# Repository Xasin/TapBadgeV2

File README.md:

# TapBadgeV2
The second, far more ambitious version of the TapBadge wearable

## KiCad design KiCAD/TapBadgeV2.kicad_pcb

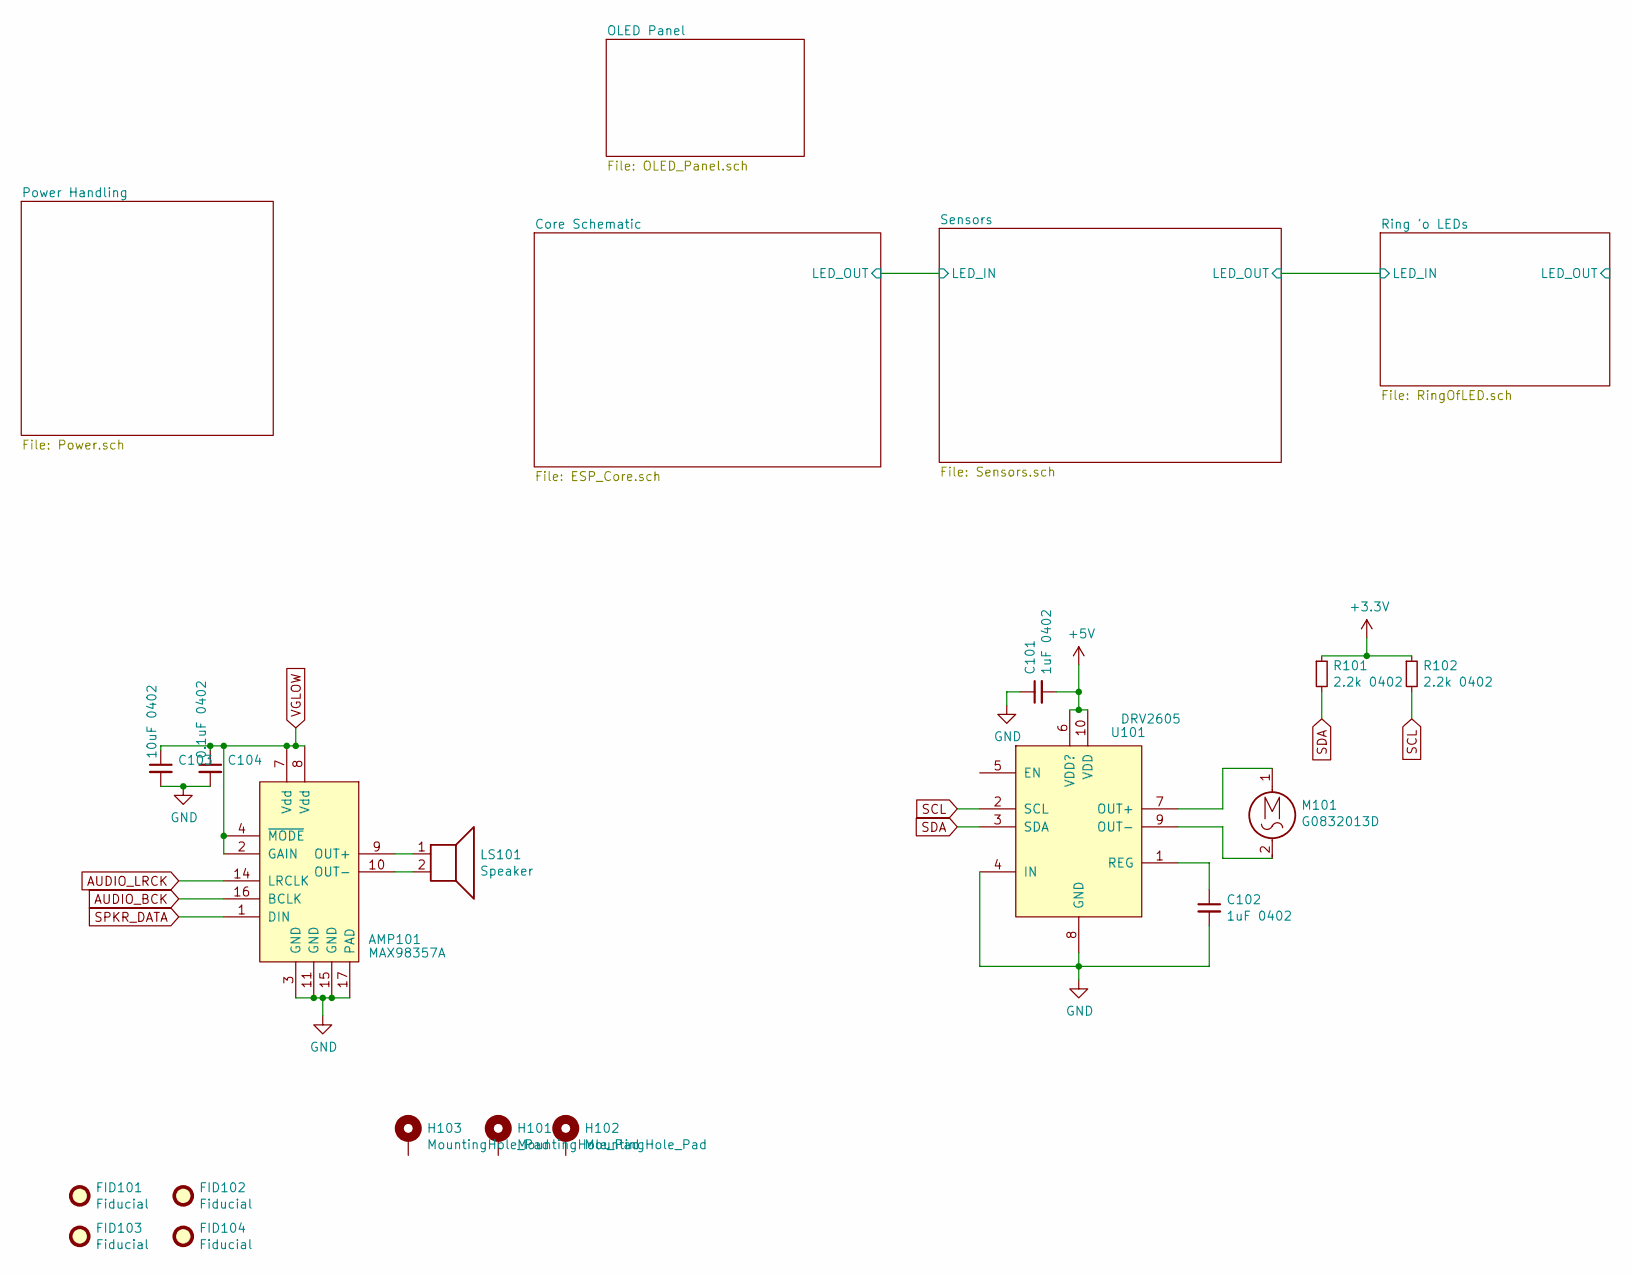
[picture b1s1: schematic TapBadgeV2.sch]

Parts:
AMP101: MAX98357A; QFN-16-1EP_3x3mm_P0.5mm_EP1.9x1.9mm_ThermalVias
C101, C102: 1uF 0402; C_0402_1005Metric
C103: 10uF 0402; C_0402_1005Metric
C104: 0.1uF 0402; C_0402_1005Metric
FID101, FID102, FID103, FID104: Fiducial; Fiducial_1mm_Mask2mm
H101, H102, H103: MountingHole_Pad; MountingHole_1.5mm_M1_Pad_Via
LS101: Speaker; SP-1609S-1
M101: G0832013D; PinHeader_1x02_P2.00mm_Vertical
R101, R102: 2.2k 0402; R_0402_1005Metric
U101: DRV2605; VSSOP-10_3x3mm_P0.5mm

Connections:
+3V3: R101.1, R102.1; also elsewhere on the board
AUDIO_BCK: AMP101.16 (BCLK); also elsewhere on the board
AUDIO_LRCK: AMP101.14 (LRCLK); also elsewhere on the board
GND: AMP101.3 (GND), AMP101.11 (GND), AMP101.15 (GND), AMP101.17 (PAD), C101.1, C102.2, C103.2, C104.2, H101.1, H102.1, H103.1, U101.4 (IN), U101.8 (GND); also elsewhere on the board
unnamed: AMP101.9 (OUT+), LS101.1
unnamed: AMP101.10 (OUT-), LS101.2
unnamed: C102.1, U101.1 (REG)
unnamed: M101.1, U101.7 (OUT+)
unnamed: M101.2, U101.9 (OUT-)
SCL: R102.2, U101.2 (SCL); also elsewhere on the board
SPKR_DATA: AMP101.1 (DIN); also elsewhere on the board

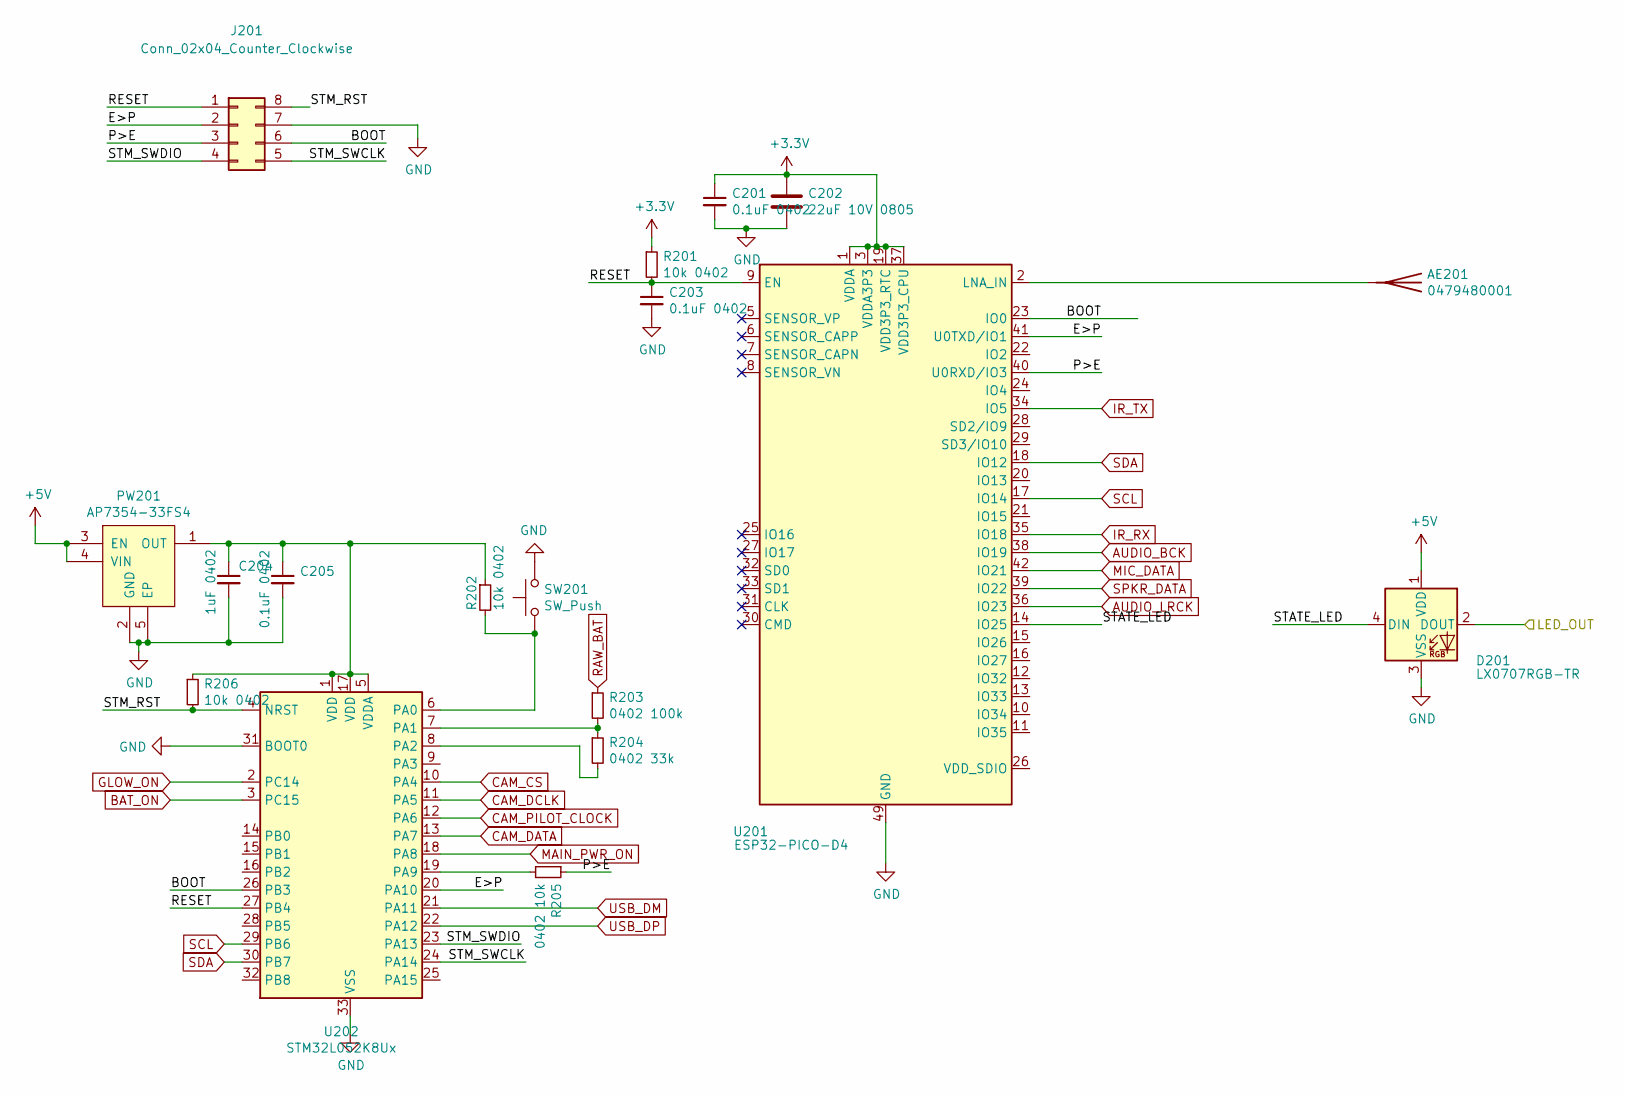
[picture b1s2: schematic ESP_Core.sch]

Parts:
AE201: 0479480001
C201, C203, C205: 0.1uF 0402; C_0402_1005Metric
C202: 22uF 10V 0805; C_0805_2012Metric
C204: 1uF 0402; C_0402_1005Metric
D201: LX0707RGB-TR; SMD-LX0707RGB-TR
J201: Conn_02x04_Counter_Clockwise; SOIC_clipProgSmall
PW201: AP7354-33FS4; X2-DFN1010-4
R201, R202, R206: 10k 0402; R_0402_1005Metric
R203: 0402 100k; R_0402_1005Metric
R204: 0402 33k; R_0402_1005Metric
R205: 0402 10k; R_0402_1005Metric
SW201: SW_Push; SW_SPST_B3U-1000P
U201: ESP32-PICO-D4; QFN-48-1EP_7x7mm_P0.5mm_EP5.3x5.3mm
U202: STM32L052K8Ux; QFN-32-1EP_5x5mm_P0.5mm_EP3.45x3.45mm

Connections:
+3V3: C201.1, C202.1, R201.1, U201.1 (VDDA), U201.3 (VDDA3P3), U201.4 (VDDA3P3), U201.19 (VDD3P3_RTC), U201.37 (VDD3P3_CPU), U201.43 (VDDA), U201.46 (VDDA); also elsewhere on the board
/Core Schematic/BOOT: J201.6, U201.23 (IO0), U202.26 (PB3)
/Core Schematic/E>P: J201.2, U201.41 (U0TXD/IO1), U202.20 (PA10)
/Core Schematic/ESP_GLOW_ON: U201.24 (IO4); also elsewhere on the board
/Core Schematic/EXT_1: U201.20 (IO13); also elsewhere on the board
/Core Schematic/EXT_2: U201.21 (IO15); also elsewhere on the board
/Core Schematic/P>E: J201.3, R205.1, U201.40 (U0RXD/IO3)
/Core Schematic/RESET: C203.1, J201.1, R201.2, U201.9 (EN), U202.27 (PB4)
/Core Schematic/STM_GLOW: U202.2 (PC14); also elsewhere on the board
/Core Schematic/STM_RST: J201.8, R206.2, U202.4 (NRST)
/Core Schematic/STM_SWCLK: J201.5, U202.24 (PA14)
/Core Schematic/STM_SWDIO: J201.4, U202.23 (PA13)
/Sensors/LED_IN: D201.2 (DOUT); also elsewhere on the board
AUDIO_BCK: U201.38 (IO19); also elsewhere on the board
AUDIO_LRCK: U201.15 (IO26); also elsewhere on the board
BAT_ON: U202.3 (PC15); also elsewhere on the board
CAM_CS: U202.10 (PA4); also elsewhere on the board
CAM_DATA: U202.13 (PA7); also elsewhere on the board
CAM_DCLK: U202.11 (PA5); also elsewhere on the board
CAM_PILOT_CLOCK: U202.12 (PA6); also elsewhere on the board
GND: C201.2, C202.2, C203.2, C204.2, C205.2, D201.3 (VSS), J201.7, PW201.2 (GND), PW201.5 (EP), SW201.2, U201.49 (GND), U202.31 (BOOT0), U202.33 (VSS); also elsewhere on the board
IR_RX: U201.16 (IO27); also elsewhere on the board
IR_TX: U201.34 (IO5); also elsewhere on the board
KNOCK_INT: U201.12 (IO32); also elsewhere on the board
MAIN_PWR_ON: U202.18 (PA8); also elsewhere on the board
unnamed: AE201.1, U201.2 (LNA_IN)
unnamed: C204.1, C205.1, PW201.1 (OUT), R202.1, R206.1, U202.1 (VDD), U202.5 (VDDA), U202.17 (VDD)
unnamed: R202.2, SW201.1, U202.6 (PA0)
unnamed: R203.2, R204.1, U202.7 (PA1)
unnamed: R204.2, U202.8 (PA2)
unnamed: R205.2, U202.19 (PA9)
RAW_BAT: R203.1; also elsewhere on the board
SCL: U201.17 (IO14), U202.29 (PB6); also elsewhere on the board
SPKR_DATA: U201.39 (IO22); also elsewhere on the board
USB_DM: U202.21 (PA11); also elsewhere on the board
USB_DP: U202.22 (PA12); also elsewhere on the board
~CHG: U202.16 (PB2); also elsewhere on the board
~VUSB_PRESENT: U202.14 (PB0); also elsewhere on the board

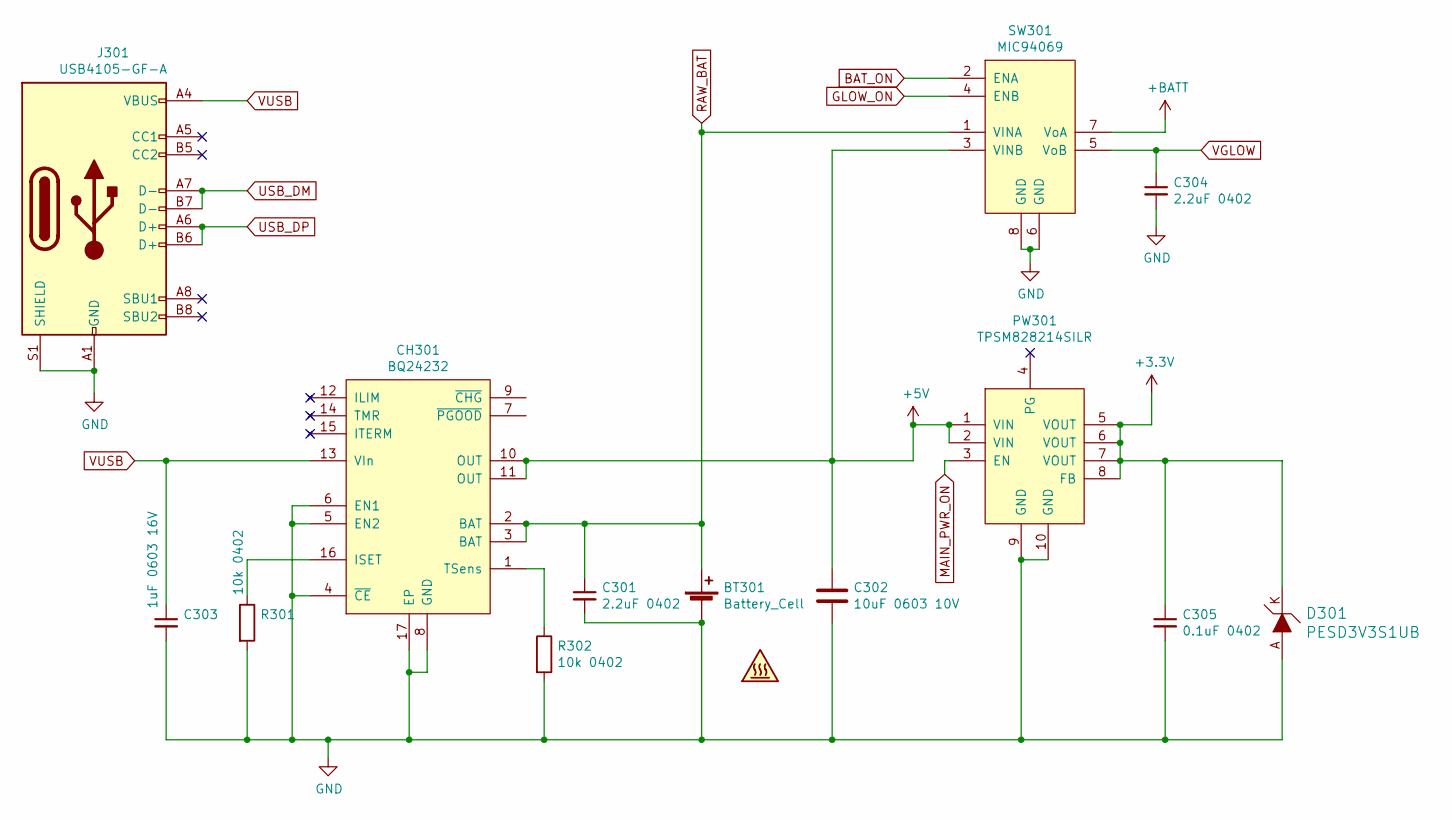
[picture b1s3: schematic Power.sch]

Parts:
BAT301: SYM_Hot_Small; LiPo_150mAh
BT301: Battery_Cell; JST_PH_S2B-PH-SM4-TB_1x02-1MP_P2.00mm_Horizontal
C301, C304: 2.2uF 0402; C_0402_1005Metric
C302: 10uF 0603 10V; C_0603_1608Metric
C303: 1uF 0603 16V; C_0603_1608Metric
C305: 0.1uF 0402; C_0402_1005Metric
CH301: BQ24232; VQFN-16-1EP_3x3mm_P0.5mm_EP1.6x1.6mm_ThermalVias
D301: PESD3V3S1UB; SOD-523; MPN ESD5Z3.3T1G; Digi-Key_PN ESD5Z3.3T1GOSCT-ND
J301: USB4105-GF-A; USB_C_Receptacle_HRO_TYPE-C-31-M-12
PW301: TPSM828214SILR; uSIP-10
R301, R302: 10k 0402; R_0402_1005Metric
SW301: MIC94069; MLF-6-EP-P0.5mm

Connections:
+3V3: C305.1, D301.K, PW301.5 (VOUT), PW301.6 (VOUT), PW301.7 (VOUT), PW301.8 (FB); also elsewhere on the board
+BATT: SW301.7 (VoA); also elsewhere on the board
GLOW_ON: SW301.4 (ENB); also elsewhere on the board
GND: BT301.2 (-), C301.2, C302.2, C303.2, C304.2, C305.2, CH301.4 (~CE), CH301.5 (EN2), CH301.6 (EN1), CH301.8 (GND), CH301.17 (EP), D301.A, J301.A1 (GND), J301.A12 (GND), J301.B1 (GND), J301.B12 (GND), J301.S1 (SHIELD), PW301.9 (GND), PW301.10 (GND), R301.2, R302.2, SW301.6 (GND), SW301.8 (GND); also elsewhere on the board
unnamed: CH301.1 (TSens), R302.1
unnamed: CH301.16 (ISET), R301.1
unnamed 73: PW301.3 (EN); also elsewhere on the board
unnamed 74: SW301.2 (ENA); also elsewhere on the board
RAW_BAT: BT301.1 (+), C301.1, CH301.2 (BAT), CH301.3 (BAT), SW301.1 (VINA); also elsewhere on the board
USB_DM: J301.A7 (D-), J301.B7 (D-); also elsewhere on the board
USB_DP: J301.A6 (D+), J301.B6 (D+); also elsewhere on the board
VUSB: C303.1, CH301.13 (VIn), J301.A4 (VBUS), J301.A9 (VBUS), J301.B4 (VBUS), J301.B9 (VBUS); also elsewhere on the board
~CHG: CH301.9 (~CHG); also elsewhere on the board
~VUSB_PRESENT: CH301.7 (~PGOOD); also elsewhere on the board

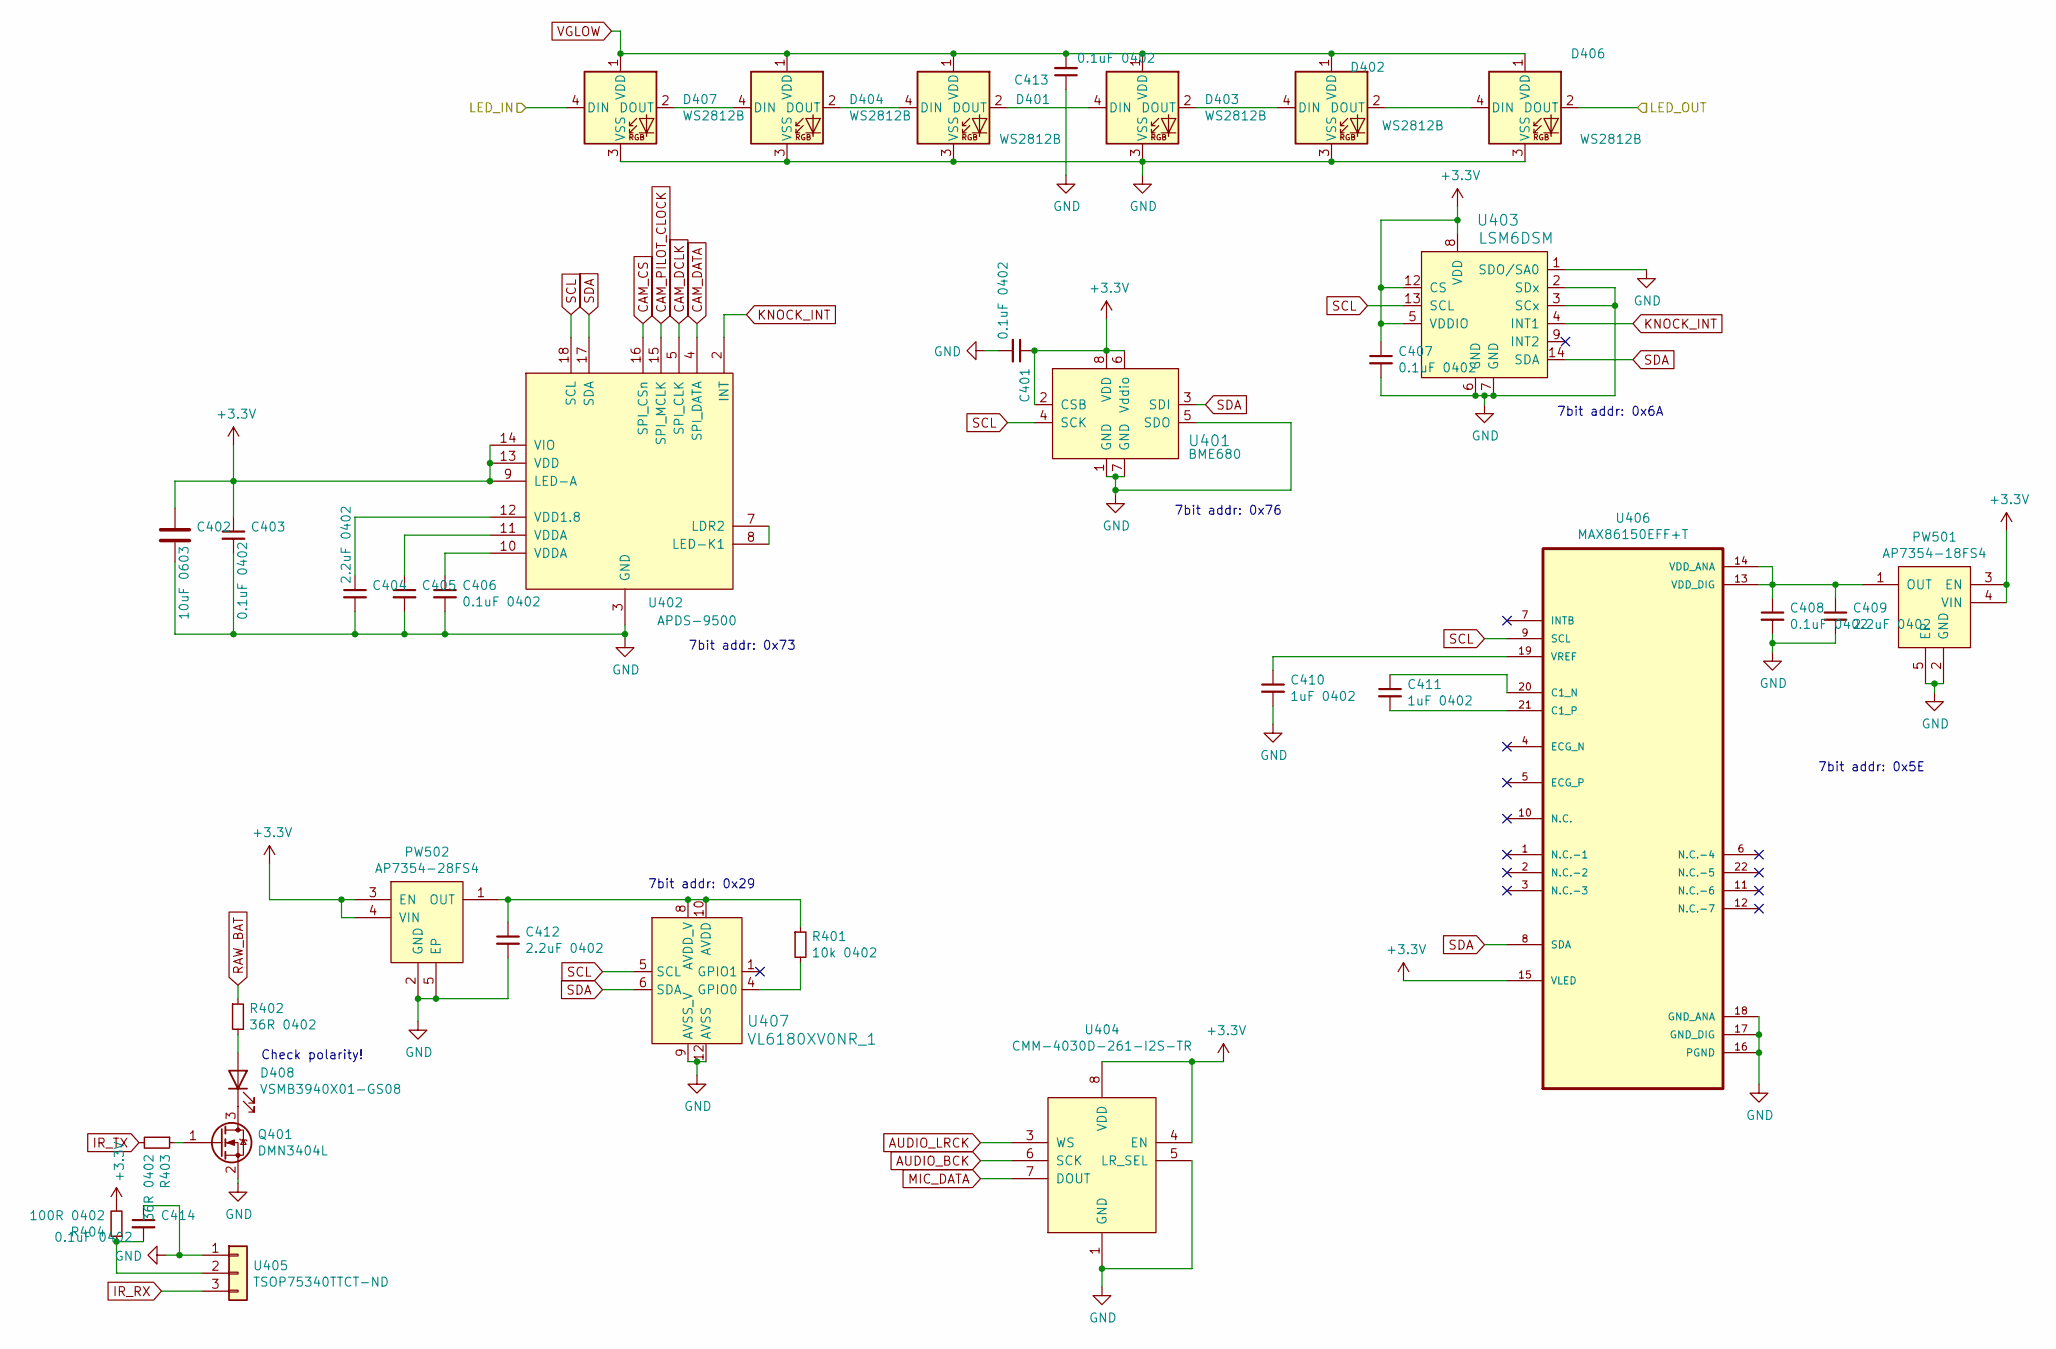
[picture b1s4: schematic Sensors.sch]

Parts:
C401, C403, C405, C406, C407, C408, C413, C414: 0.1uF 0402; C_0402_1005Metric
C402: 10uF 0603; C_0603_1608Metric
C404, C409, C412: 2.2uF 0402; C_0402_1005Metric
C410, C411: 1uF 0402; C_0402_1005Metric
D401, D402, D403, D404, D406, D407: WS2812B; SMD-LX0707RGB-TR
D408: VSMB3940X01-GS08; LED_PLCC-2
PW501: AP7354-18FS4; X2-DFN1010-4
PW502: AP7354-28FS4; X2-DFN1010-4
Q401: DMN3404L; SOT-23
R401: 10k 0402; R_0402_1005Metric
R402, R403: 36R 0402; R_0402_1005Metric
R404: 100R 0402; R_0402_1005Metric
U401: BME680; MPN BME680; Digi-Key_PN 828-1077-1-ND
U402: APDS-9500
U403: LSM6DSM; LGA-14L_2.5x3mm__LSM6DS3; MPN LSM6DS3TR; Digi-Key_PN 497-15383-1-ND
U404: CMM-4030D-261-I2S-TR; CMM-4030
U405: TSOP75340TTCT-ND; TSOP75xxx
U406: MAX86150EFF+T; XDCR_MAX86150EFF+
U407: VL6180XV0NR_1; LGA-12_4.8x2.8_VL6180; MPN VL6180XV0NR/1; Digi-Key_PN 497-14702-1-ND

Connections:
+3V3: C401.1, C402.1, C403.1, C407.1, PW501.3 (EN), PW501.4 (VIN), PW502.3 (EN), PW502.4 (VIN), R404.2, U401.2 (CSB), U401.6 (Vddio), U401.8 (VDD), U402.9 (LED-A), U402.13 (VDD), U402.14 (VIO), U403.5 (VDDIO), U403.8 (VDD), U403.12 (CS), U404.4 (EN), U404.8 (VDD), U406.15 (VLED); also elsewhere on the board
/Ring 'o LEDs/LED_IN: D406.2 (DOUT); also elsewhere on the board
/Sensors/LED_IN: D407.4 (DIN); also elsewhere on the board
AUDIO_BCK: U404.6 (SCK); also elsewhere on the board
AUDIO_LRCK: U404.3 (WS); also elsewhere on the board
CAM_CS: U402.16 (SPI_CSn); also elsewhere on the board
CAM_DATA: U402.4 (SPI_DATA); also elsewhere on the board
CAM_DCLK: U402.5 (SPI_CLK); also elsewhere on the board
CAM_PILOT_CLOCK: U402.15 (SPI_MCLK); also elsewhere on the board
GND: C401.2, C402.2, C403.2, C404.2, C405.2, C406.2, C407.2, C408.2, C409.2, C410.2, C412.2, C413.1, C414.1, D401.3 (VSS), D402.3 (VSS), D403.3 (VSS), D404.3 (VSS), D406.3 (VSS), D407.3 (VSS), PW501.2 (GND), PW501.5 (EP), PW502.2 (GND), PW502.5 (EP), Q401.2 (S), U401.1 (GND), U401.5 (SDO), U401.7 (GND), U402.3 (GND), U403.1 (SDO/SA0), U403.2 (SDx), U403.3 (SCx), U403.6 (GND), U403.7 (GND), U404.1 (GND), U404.5 (LR_SEL), U405.1, U406.16 (PGND), U406.17 (GND_DIG), U406.18 (GND_ANA), U407.9 (AVSS_V), U407.12 (AVSS); also elsewhere on the board
IR_RX: U405.3; also elsewhere on the board
IR_TX: R403.2; also elsewhere on the board
KNOCK_INT: U402.2 (INT), U403.4 (INT1); also elsewhere on the board
unnamed: C404.1, U402.12 (VDD1.8)
unnamed: C405.1, U402.11 (VDDA)
unnamed: C406.1, U402.10 (VDDA)
unnamed: C408.1, C409.1, PW501.1 (OUT), U406.13 (VDD_DIG), U406.14 (VDD_ANA)
unnamed: C410.1, U406.19 (VREF)
unnamed: C411.1, U406.20 (C1_N)
unnamed: C411.2, U406.21 (C1_P)
unnamed: C412.1, PW502.1 (OUT), R401.1, U407.8 (AVDD_V), U407.10 (AVDD)
unnamed: C414.2, R404.1, U405.2
unnamed: D401.2 (DOUT), D403.4 (DIN)
unnamed: D401.4 (DIN), D404.2 (DOUT)
unnamed: D402.2 (DOUT), D406.4 (DIN)
unnamed: D402.4 (DIN), D403.2 (DOUT)
unnamed: D404.4 (DIN), D407.2 (DOUT)
unnamed: D408.1 (K), Q401.3 (D)
unnamed: D408.2 (A), R402.2
unnamed: Q401.1 (G), R403.1
unnamed: R401.2, U407.4 (GPIO0)
unnamed: U402.7 (LDR2), U402.8 (LED-K1)
RAW_BAT: R402.1; also elsewhere on the board
SCL: U401.4 (SCK), U402.18 (SCL), U403.13 (SCL), U406.9 (SCL), U407.5 (SCL); also elsewhere on the board

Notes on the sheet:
Check polarity!
7bit addr: 0x76
7bit addr: 0x6A
7bit addr: 0x73
7bit addr: 0x29
7bit addr: 0x5E

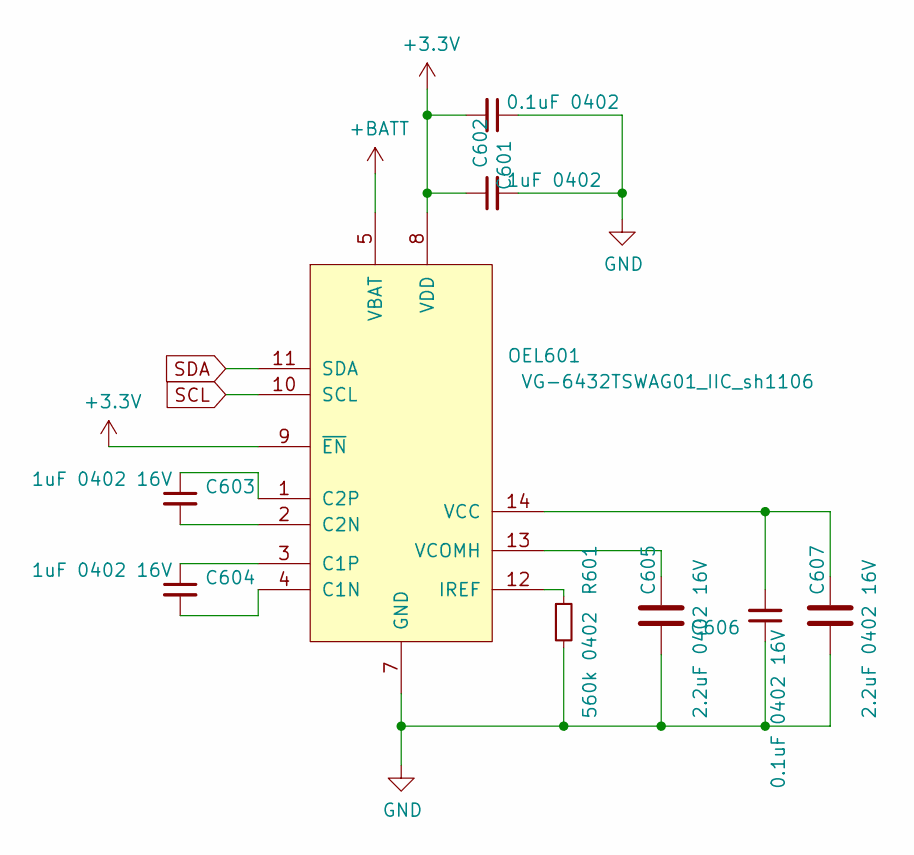
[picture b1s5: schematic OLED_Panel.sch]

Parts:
C601: 0.1uF 0402; C_0402_1005Metric
C602: 1uF 0402; C_0402_1005Metric
C603, C604: 1uF 0402 16V; C_0402_1005Metric
C605, C607: 2.2uF 0402 16V; C_0402_1005Metric
C606: 0.1uF 0402 16V; C_0402_1005Metric
OEL601: VG-6432TSWAG01_IIC_sh1106; OLED_Smoll_Upsidedown
R601: 560k 0402; R_0402_1005Metric

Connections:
+3V3: C601.2, C602.1, OEL601.8 (VDD), OEL601.9 (~EN); also elsewhere on the board
+BATT: OEL601.5 (VBAT); also elsewhere on the board
GND: C601.1, C602.2, C605.2, C606.1, C607.2, OEL601.7 (GND), R601.2; also elsewhere on the board
unnamed: C603.1, OEL601.1 (C2P)
unnamed: C603.2, OEL601.2 (C2N)
unnamed: C604.1, OEL601.3 (C1P)
unnamed: C604.2, OEL601.4 (C1N)
unnamed: C605.1, OEL601.13 (VCOMH)
unnamed: C606.2, C607.1, OEL601.14 (VCC)
unnamed: OEL601.12 (IREF), R601.1
SCL: OEL601.10 (SCL); also elsewhere on the board

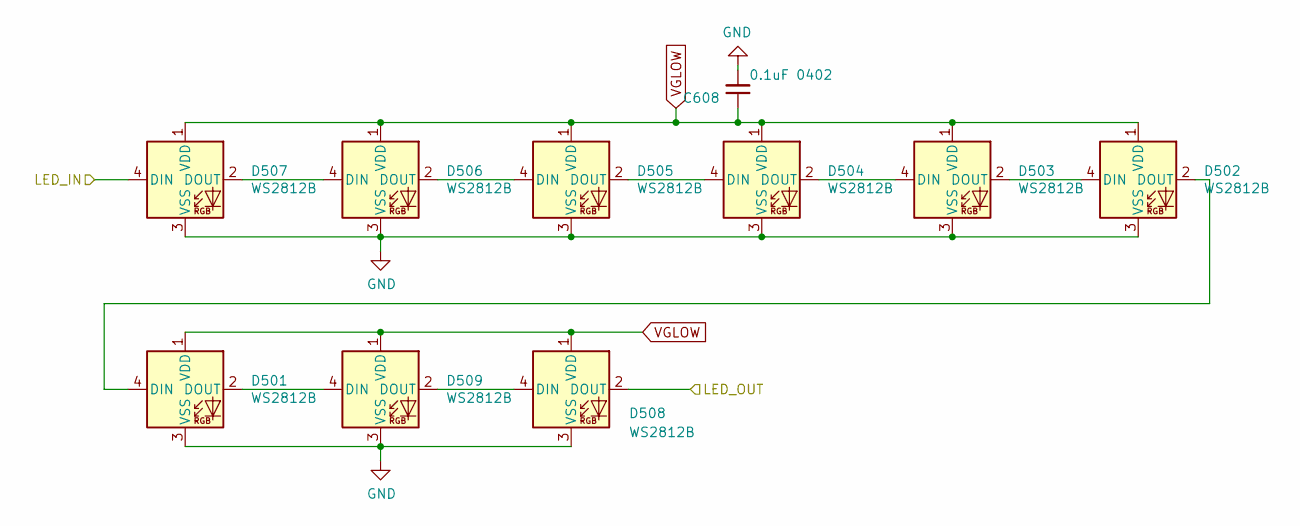
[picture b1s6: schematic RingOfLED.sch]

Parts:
C608: 0.1uF 0402; C_0402_1005Metric
D501, D502, D503, D504, D505, D506, D507, D508, D509: WS2812B; IN-PI42TAS

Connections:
/Ring 'o LEDs/LED_IN: D507.4 (DIN); also elsewhere on the board
/Ring 'o LEDs/LED_OUT: D508.2 (DOUT)
GND: C608.2, D501.3 (VSS), D502.3 (VSS), D503.3 (VSS), D504.3 (VSS), D505.3 (VSS), D506.3 (VSS), D507.3 (VSS), D508.3 (VSS), D509.3 (VSS); also elsewhere on the board
unnamed: D501.2 (DOUT), D509.4 (DIN)
unnamed: D501.4 (DIN), D502.2 (DOUT)
unnamed: D502.4 (DIN), D503.2 (DOUT)
unnamed: D503.4 (DIN), D504.2 (DOUT)
unnamed: D504.4 (DIN), D505.2 (DOUT)
unnamed: D505.4 (DIN), D506.2 (DOUT)
unnamed: D506.4 (DIN), D507.2 (DOUT)
unnamed: D508.4 (DIN), D509.2 (DOUT)

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
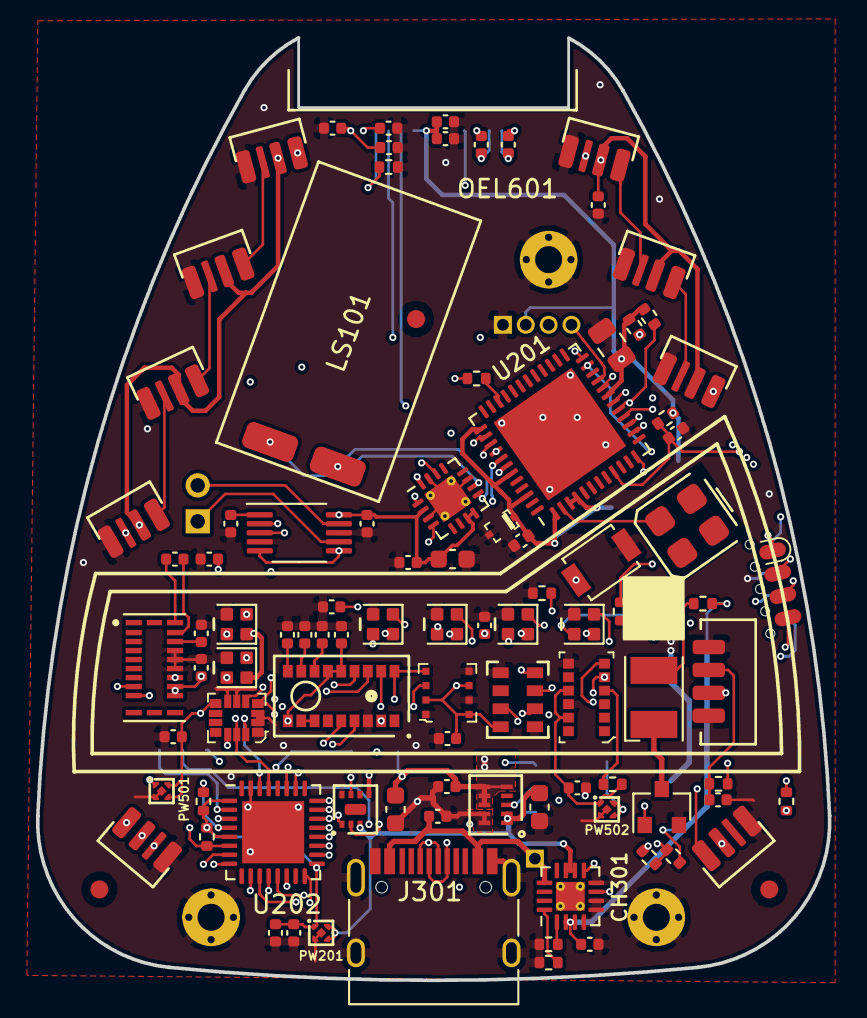
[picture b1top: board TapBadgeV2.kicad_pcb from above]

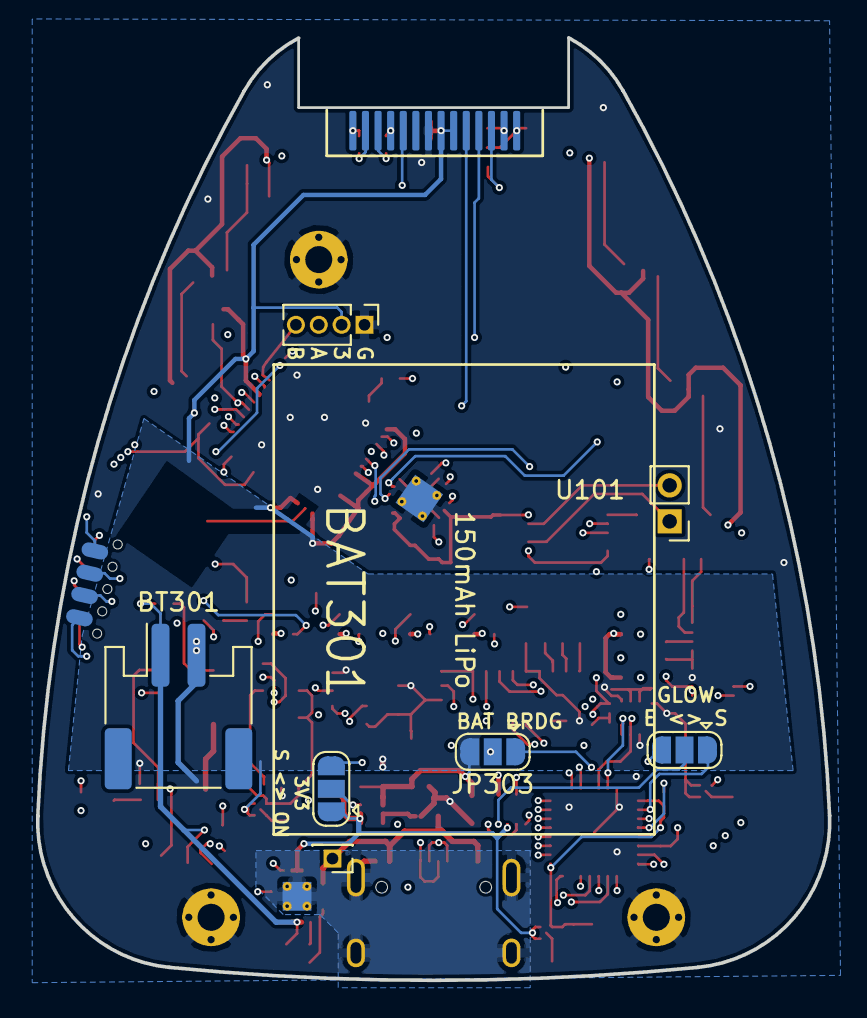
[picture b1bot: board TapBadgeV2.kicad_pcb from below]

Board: 4 copper layers, 44.0 x 52.4 mm, 110 parts (9 on the bottom side), 91 nets.

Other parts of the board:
J202: Conn_01x04_Female; PinHeader_1x04_P1.27mm_Vertical
JP201, JP302, JP303: SolderJumper_3_Bridged12; SolderJumper-3_P1.3mm_Open_RoundedPad1.0x1.5mm
R207: 36R 0402; R_0402_1005Metric
R208: 10k 0402; R_0402_1005Metric
SYM101: SYM_Radioactive_Large; DragonIcon_7mm_Solder
TP301: TestPoint; PinHeader_1x01_P1.27mm_Vertical

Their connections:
+3V3: J202.2, JP303.3; also elsewhere on the board
/Core Schematic/ESP_GLOW_ON: JP201.3; also elsewhere on the board
/Core Schematic/EXT_1: J202.3; also elsewhere on the board
/Core Schematic/EXT_2: J202.4; also elsewhere on the board
/Core Schematic/STM_GLOW: JP201.1; also elsewhere on the board
BAT_ON: JP303.1; also elsewhere on the board
GLOW_ON: JP201.2; also elsewhere on the board
GND: J202.1, R208.1; also elsewhere on the board
MAIN_PWR_ON: JP302.3; also elsewhere on the board
unnamed 73: JP302.2; also elsewhere on the board
unnamed 74: JP303.2; also elsewhere on the board
VUSB: TP301.1; also elsewhere on the board

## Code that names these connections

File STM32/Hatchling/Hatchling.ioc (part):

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Mcu.Name=STM32L052K(6-8)Ux
Mcu.Package=UFQFPN32
Mcu.UserName=STM32L052K8Ux
PA0.Mode=SYS_WakeUp0
PA0.Signal=SYS_WKUP1
PA1.Mode=IN1
PA1.Signal=ADC_IN1
PA10.Mode=Asynchronous
PA10.Signal=USART1_RX
PA11.Mode=Device
PA11.Signal=USB_DM
PA12.Mode=Device
PA12.Signal=USB_DP
PA13.Mode=Serial_Wire
PA13.Signal=SYS_SWDIO
PA14.Mode=Serial_Wire
PA14.Signal=SYS_SWCLK
PA2.Signal=GPIO_Output
PA4.Mode=NSS_Signal_Hard_Input
PA4.Signal=SPI1_NSS
PA5.Mode=RX_Only_Simplex_Unidirect_Slave
PA5.Signal=SPI1_SCK
PA6.Signal=S_TIM22_CH1
PA7.Mode=RX_Only_Simplex_Unidirect_Slave
PA7.Signal=SPI1_MOSI
PA8.Signal=GPIO_Output
PA9.Mode=Asynchronous
PA9.Signal=USART1_TX
PB3.Signal=GPIO_Output
PB4.Signal=GPIO_Output
PB5.Signal=S_TIM22_CH2
PB6.Mode=I2C
PB6.Signal=I2C1_SCL
PB7.Mode=I2C
PB7.Signal=I2C1_SDA
PC14-OSC32_IN.Signal=GPIO_Output
PC15-OSC32_OUT.Signal=GPIO_Output
RCC.SYSCLKFreq_VALUE=2097000
board=custom

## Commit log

2021-07-29 First proper commit of Tap's schematic!
2021-08-01 Continue work on Schematics
2021-08-30 Add STM32 base circuit for power control and USB, also a lot of other things
2021-08-30 Add STM32 workspace
2021-09-08 Continue work on TapV2's schematic, almost completing it!
2021-09-28 Finalize PCB schematics
2021-10-15 Begin work on testing Tap
2021-10-15 Add clicks for upcoming click engine
2021-10-15 Bump XasCode version
2021-10-17 Continued playing
2021-10-18 Continue monch-work
